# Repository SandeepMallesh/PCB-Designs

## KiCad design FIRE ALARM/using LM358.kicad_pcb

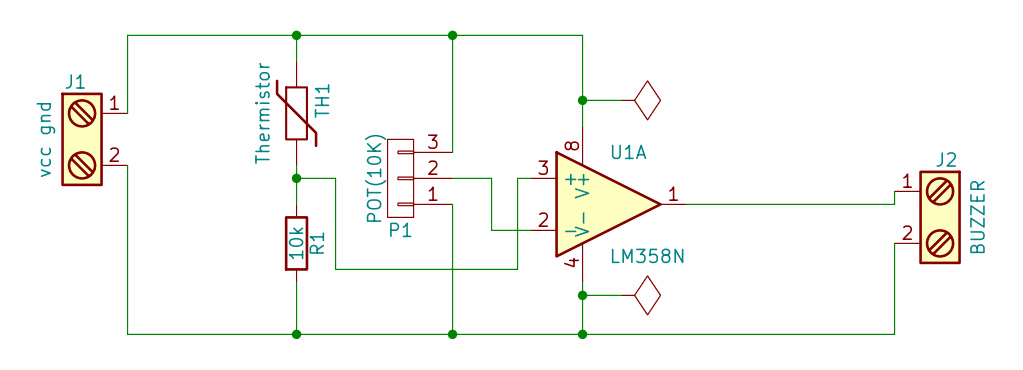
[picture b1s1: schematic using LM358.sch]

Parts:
J1: vcc gnd; bornier2
J2: BUZZER; bornier2
P1: POT(10K); Pin_Header_Straight_1x03_Pitch2.54mm
R1: 10k; Resistor_Horizontal_RM7mm
TH1: Thermistor; Pin_Header_Straight_1x02_Pitch1.27mm
U1: LM358N; DIP-8_W7.62mm

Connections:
unnamed: J1.1, P1.3, TH1.1, U1.8 (V+)
unnamed: J1.2, J2.2, P1.1, R1.2, U1.4 (V-)
unnamed: J2.1, U1.1
unnamed: P1.2, U1.2 (-)
unnamed: R1.1, TH1.2, U1.3 (+)

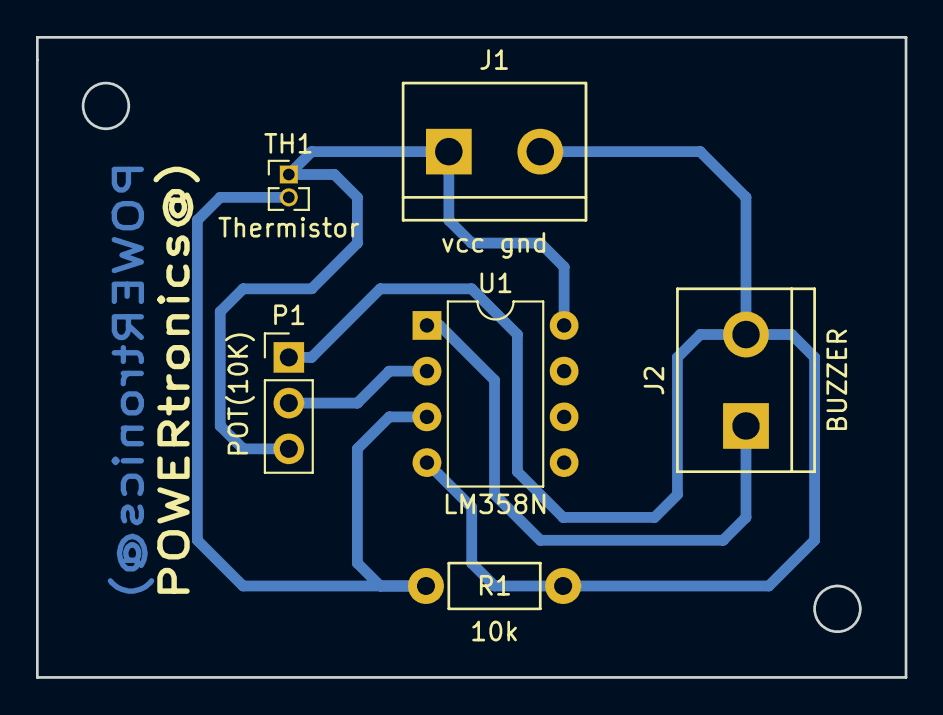
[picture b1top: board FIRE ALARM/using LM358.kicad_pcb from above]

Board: 2 copper layers, 48.3 x 35.6 mm, 6 parts (0 on the bottom side), 5 nets.

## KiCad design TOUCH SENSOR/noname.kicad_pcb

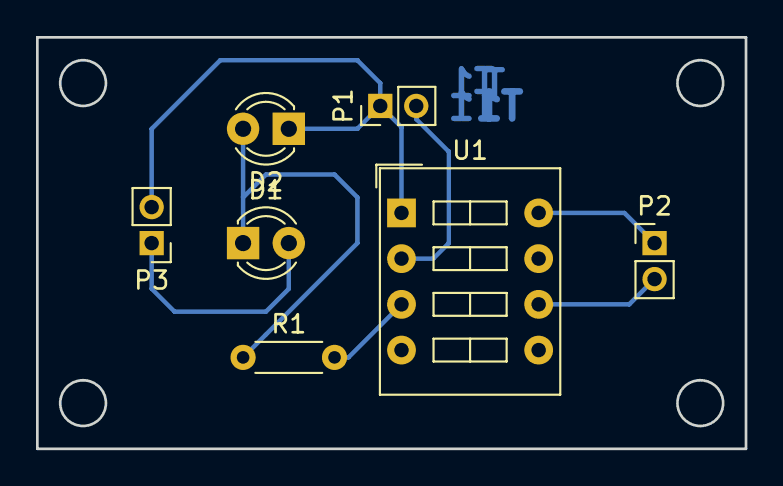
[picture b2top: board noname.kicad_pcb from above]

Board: 2 copper layers, 39.4 x 22.9 mm, 7 parts (0 on the bottom side), 7 nets.

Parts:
D1, D2: LED; LED_D3.0mm_FlatTop
P1, P2, P3: CONN_01X02; Pin_Header_Straight_1x02_Pitch2.00mm
R1: R; R_Axial_DIN0204_L3.6mm_D1.6mm_P5.08mm_Horizontal
U1: NE555; SW_DIP_x4_W7.62mm_Slide

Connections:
GND: D2.1, P1.1, P3.2, U1.1
unnamed: D1.1, D2.2, R1.1
unnamed: D1.2, P3.1
unnamed: P1.2, U1.2
unnamed: P2.2, U1.6
unnamed: R1.2, U1.3
VCC: P2.1, U1.8

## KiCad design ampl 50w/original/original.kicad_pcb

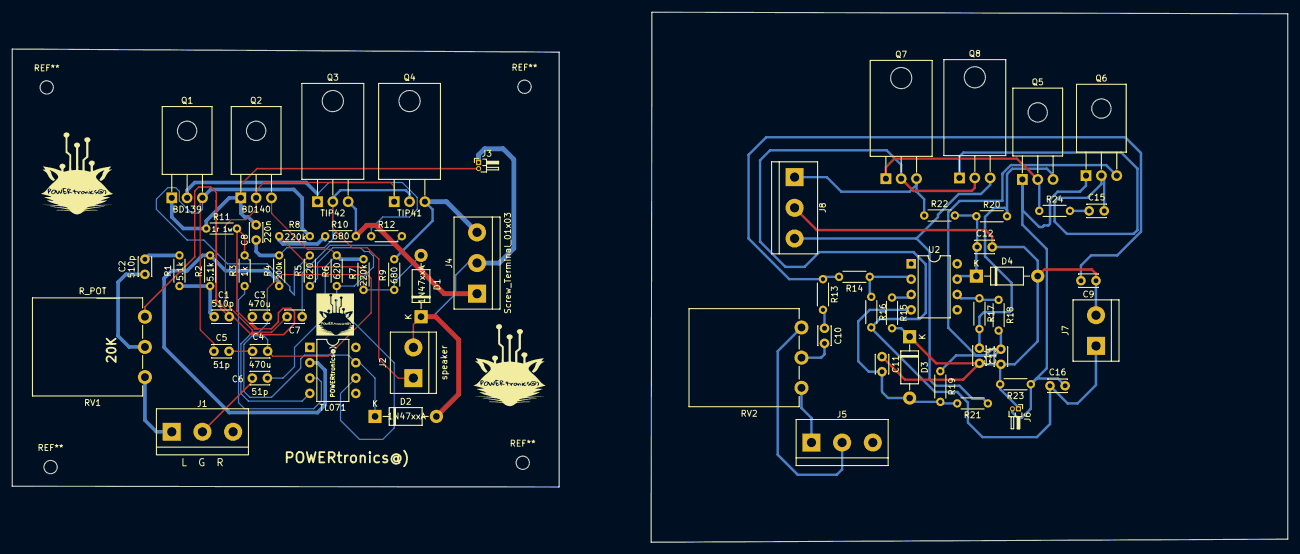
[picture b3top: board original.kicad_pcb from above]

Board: 2 copper layers, 211.2 x 87.8 mm, 64 parts (0 on the bottom side), 35 nets.

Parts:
C1, C2, C9, C10: 510p; C_Disc_D3.0mm_W2.0mm_P2.50mm
C3, C4, C11, C12: 470u; C_Disc_D3.0mm_W2.0mm_P2.50mm
C5, C6, C13, C14: 51p; C_Disc_D3.0mm_W2.0mm_P2.50mm
C7, C15: 100n; C_Disc_D3.0mm_W2.0mm_P2.50mm
C8, C16: 220n; C_Disc_D3.0mm_W2.0mm_P2.50mm
D1, D2, D3, D4: 1N47xxA; D_DO-41_SOD81_P10.16mm_Horizontal
J1, J5: L G R; TerminalBlock_bornier-3_P5.08mm
J2, J7: speaker; TerminalBlock_bornier-2_P5.08mm
J3, J6: jumper; PinHeader_1x02_P1.00mm_Horizontal
J4, J8: Screw_Terminal_01x03; TerminalBlock_bornier-3_P5.08mm
Q1, Q5: BD139; TO-126_Horizontal
Q2, Q6: BD140; TO-126_Horizontal
Q3, Q7: TIP42; TO-220-3_Horizontal
Q4, Q8: TIP41; TO-220-3_Horizontal
R1, R2, R13, R14: 5.1k; R_Axial_DIN0204_L3.6mm_D1.6mm_P5.08mm_Horizontal
R3, R12, R15, R24: 1k; R_Axial_DIN0204_L3.6mm_D1.6mm_P5.08mm_Horizontal
R4, R16: 200k; R_Axial_DIN0204_L3.6mm_D1.6mm_P5.08mm_Horizontal
R5, R6, R17, R18: 620; R_Axial_DIN0204_L3.6mm_D1.6mm_P5.08mm_Horizontal
R7, R8, R19, R20: 220k; R_Axial_DIN0204_L3.6mm_D1.6mm_P5.08mm_Horizontal
R9, R10, R21, R22: 680; R_Axial_DIN0204_L3.6mm_D1.6mm_P5.08mm_Horizontal
R11, R23: 1r 1w; R_Axial_DIN0204_L3.6mm_D1.6mm_P5.08mm_Horizontal
RV1, RV2: R_POT; Potentiometer_Piher_PC-16_Single_Vertical
U1, U2: TL071; DIP-8_W7.62mm

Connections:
GND: C1.1, C3.1, C4.2, C5.2, C6.1, C9.1, C11.1, C12.2, C13.2, C14.1, D1.1, D2.2, D3.1, D4.2, J1.2, J2.2, J3.1, J4.2, J5.2, J6.1, J7.2, J8.2, R3.2, R11.2, R15.2, R23.2, RV1.1, RV2.1
unnamed: C1.2, R1.1, R2.2
unnamed: C2.1, R1.2
unnamed: C2.2, RV1.2
unnamed: C3.2, D1.2, R7.2, R9.2, U1.4
unnamed: C4.1, D2.1, R8.1, R10.2, U1.7
unnamed: C5.1, Q1.3, R5.2, R8.2
unnamed: C6.2, Q2.3, R6.2, R7.1
unnamed: C7.1, R12.2
unnamed: C7.2, Q2.2, Q4.1
unnamed: C8.1, J2.1, Q3.2, Q4.2, R4.2
unnamed: C8.2, J3.2, Q1.1, Q2.1, R11.1
unnamed: C9.2, R13.1, R14.2
unnamed: C10.1, R13.2
unnamed: C10.2, RV2.2
unnamed: C11.2, D3.2, R19.2, R21.2, U2.4
unnamed: C12.1, D4.1, R20.1, R22.2, U2.7
unnamed: C13.1, Q5.3, R17.2, R20.2
unnamed: C14.2, Q6.3, R18.2, R19.1
unnamed: C15.1, R24.2
unnamed: C15.2, Q6.2, Q8.1
unnamed: C16.1, J7.1, Q7.2, Q8.2, R16.2
unnamed: C16.2, J6.2, Q5.1, Q6.1, R23.1
unnamed: J1.1, RV1.3
unnamed: J5.1, RV2.3
unnamed: Q1.2, Q3.1, R12.1
unnamed: Q5.2, Q7.1, R24.1
unnamed: R2.1, R4.1, U1.2
unnamed: R3.1, U1.3
unnamed: R5.1, R6.1, U1.6
unnamed: R14.1, R16.1, U2.2
unnamed: R15.1, U2.3
unnamed: R17.1, R18.1, U2.6
VCC: J4.1, J8.1, Q3.3, Q7.3, R10.1, R22.1
VEE: J4.3, J8.3, Q4.3, Q8.3, R9.1, R21.1

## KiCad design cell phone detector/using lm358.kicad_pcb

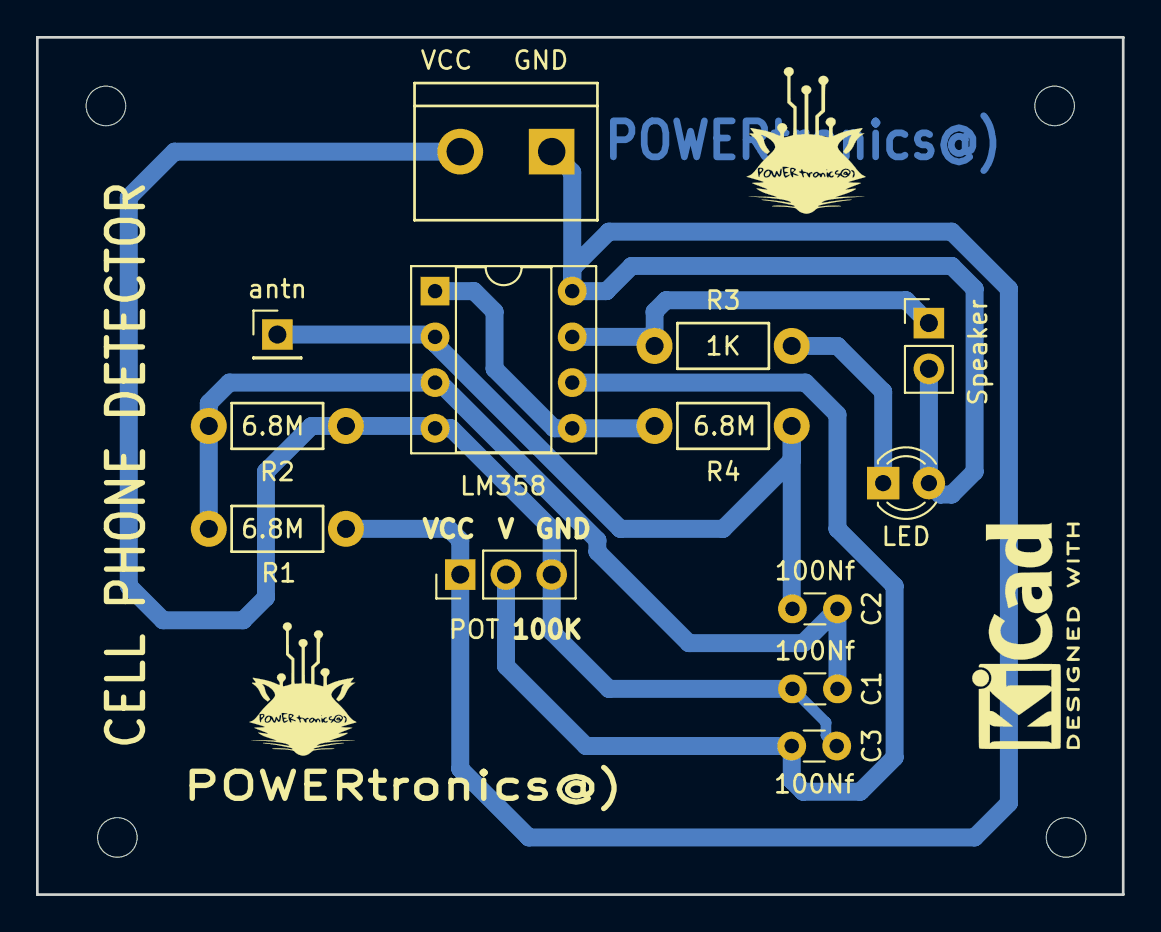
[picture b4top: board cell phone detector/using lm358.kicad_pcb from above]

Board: 2 copper layers, 60.3 x 47.6 mm, 13 parts (0 on the bottom side), 8 nets.

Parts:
C1, C2, C3: 100Nf; C_Disc_D3.0mm_W1.6mm_P2.50mm
D1: LED; LED_D3.0mm
J1: VCC GND; bornier2
LS1: Speaker; Pin_Header_Straight_1x02_Pitch2.54mm
P1: antn; Pin_Header_Straight_1x01_Pitch2.54mm
P2: POT; Pin_Header_Straight_1x03_Pitch2.54mm
R1, R2, R3: 6.8M; Resistor_Horizontal_RM7mm
R4: 1K; Resistor_Horizontal_RM7mm
U1: LM358; DIP-8_W7.62mm_Socket

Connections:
unnamed: C1.1, C2.1, R1.2, R2.1, U1.3
unnamed: C1.2, C3.2, J1.2, P2.3, R2.2, U1.4
unnamed: C2.2, P1.1, R3.2, U1.2
unnamed: C3.1, P2.2, U1.6
unnamed: D1.1, R4.1
unnamed: D1.2, J1.1, LS1.2, P2.1, R1.1, U1.8
unnamed: LS1.1, R4.2, U1.7
unnamed: R3.1, U1.1, U1.5
